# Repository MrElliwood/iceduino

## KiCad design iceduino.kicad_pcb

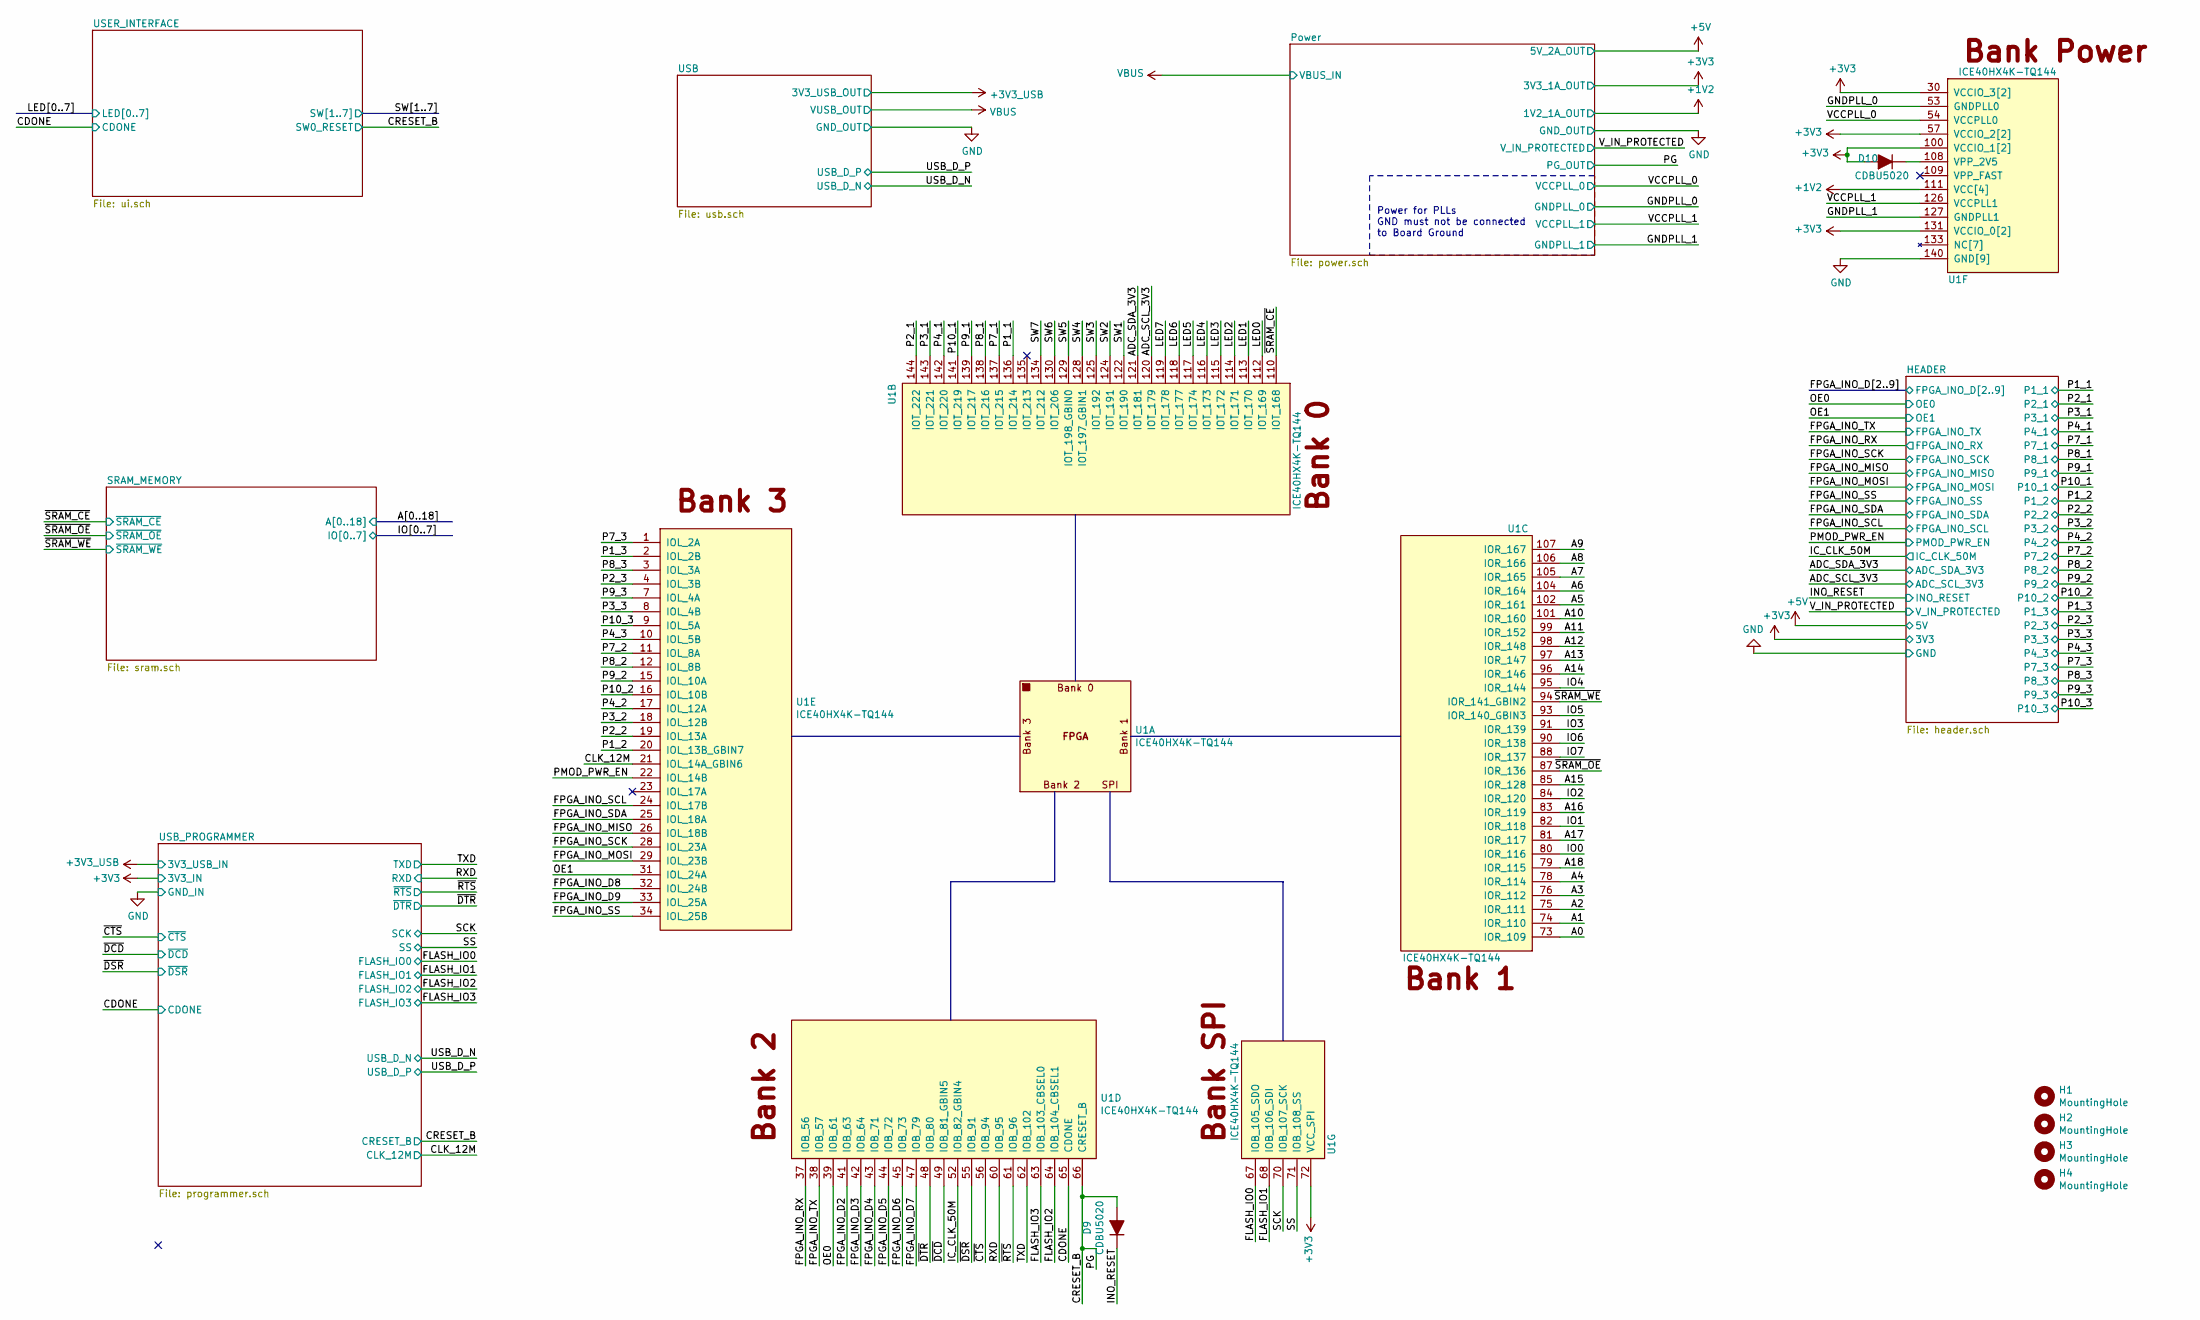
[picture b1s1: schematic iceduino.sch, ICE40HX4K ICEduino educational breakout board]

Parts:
D9, D10: CDBU5020; D_0603_1608Metric; Mfg Part Num CDBU0520; Digikey 641-1332-1-ND
H1, H2, H3, H4: MountingHole; MountingHole_3mm
U1: ICE40HX4K-TQ144; TQFP-144_20x20mm_P0.5mm; Mfg Part Num ICE40HX4K-TQ144; Digikey 220-1572-ND

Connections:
+1V2: U1.27 (VCC), U1.40 (VCC), U1.92 (VCC), U1.111 (VCC[4]); also elsewhere on the board
+3V3: D10.2 (A), U1.6 (VCCIO_3), U1.30 (VCCIO_3[2]), U1.46 (VCCIO_2), U1.57 (VCCIO_2[2]), U1.72 (VCC_SPI), U1.89 (VCCIO_1), U1.100 (VCCIO_1[2]), U1.123 (VCCIO_0), U1.131 (VCCIO_0[2]); also elsewhere on the board
/A0: U1.73 (IOR_109); also elsewhere on the board
/A1: U1.74 (IOR_110); also elsewhere on the board
/A2: U1.75 (IOR_111); also elsewhere on the board
/A3: U1.76 (IOR_112); also elsewhere on the board
/A4: U1.78 (IOR_114); also elsewhere on the board
/A5: U1.102 (IOR_161); also elsewhere on the board
/A6: U1.104 (IOR_164); also elsewhere on the board
/A7: U1.105 (IOR_165); also elsewhere on the board
/A8: U1.106 (IOR_166); also elsewhere on the board
/A9: U1.107 (IOR_167); also elsewhere on the board
/A10: U1.101 (IOR_160); also elsewhere on the board
/A11: U1.99 (IOR_152); also elsewhere on the board
/A12: U1.98 (IOR_148); also elsewhere on the board
/A13: U1.97 (IOR_147); also elsewhere on the board
/A14: U1.96 (IOR_146); also elsewhere on the board
/A15: U1.85 (IOR_128); also elsewhere on the board
/A16: U1.83 (IOR_119); also elsewhere on the board
/A17: U1.81 (IOR_117); also elsewhere on the board
/A18: U1.79 (IOR_115); also elsewhere on the board
/ADC_SCL_3V3: U1.120 (IOT_179); also elsewhere on the board
/ADC_SDA_3V3: U1.121 (IOT_181); also elsewhere on the board
/CDONE: U1.65 (CDONE); also elsewhere on the board
/CLK_12M: U1.21 (IOL_14A_GBIN6); also elsewhere on the board
/CRESET_B: D9.2 (A), U1.66 (CRESET_B); also elsewhere on the board
/FLASH_IO0: U1.67 (IOB_105_SDO); also elsewhere on the board
/FLASH_IO1: U1.68 (IOB_106_SDI); also elsewhere on the board
/FLASH_IO2: U1.64 (IOB_104_CBSEL1); also elsewhere on the board
/FLASH_IO3: U1.63 (IOB_103_CBSEL0); also elsewhere on the board
/FPGA_INO_D2: U1.41 (IOB_63); also elsewhere on the board
/FPGA_INO_D3: U1.42 (IOB_64); also elsewhere on the board
/FPGA_INO_D4: U1.43 (IOB_71); also elsewhere on the board
/FPGA_INO_D5: U1.44 (IOB_72); also elsewhere on the board
/FPGA_INO_D6: U1.45 (IOB_73); also elsewhere on the board
/FPGA_INO_D7: U1.47 (IOB_79); also elsewhere on the board
/FPGA_INO_D8: U1.32 (IOL_24B); also elsewhere on the board
/FPGA_INO_D9: U1.33 (IOL_25A); also elsewhere on the board
/FPGA_INO_MISO: U1.26 (IOL_18B); also elsewhere on the board
/FPGA_INO_MOSI: U1.29 (IOL_23B); also elsewhere on the board
/FPGA_INO_RX: U1.37 (IOB_56); also elsewhere on the board
/FPGA_INO_SCK: U1.28 (IOL_23A); also elsewhere on the board
/FPGA_INO_SCL: U1.24 (IOL_17B); also elsewhere on the board
/FPGA_INO_SDA: U1.25 (IOL_18A); also elsewhere on the board
/FPGA_INO_SS: U1.34 (IOL_25B); also elsewhere on the board
/FPGA_INO_TX: U1.38 (IOB_57); also elsewhere on the board
/GNDPLL_0: U1.53 (GNDPLL0); also elsewhere on the board
/GNDPLL_1: U1.127 (GNDPLL1); also elsewhere on the board
/IC_CLK_50M: U1.52 (IOB_82_GBIN4); also elsewhere on the board
/INO_RESET: D9.1 (K); also elsewhere on the board
/IO0: U1.80 (IOR_116); also elsewhere on the board
/IO1: U1.82 (IOR_118); also elsewhere on the board
/IO2: U1.84 (IOR_120); also elsewhere on the board
/IO3: U1.91 (IOR_139); also elsewhere on the board
/IO4: U1.95 (IOR_144); also elsewhere on the board
/IO5: U1.93 (IOR_140_GBIN3); also elsewhere on the board
/IO6: U1.90 (IOR_138); also elsewhere on the board
/IO7: U1.88 (IOR_137); also elsewhere on the board
/LED0: U1.112 (IOT_169); also elsewhere on the board
/LED1: U1.113 (IOT_170); also elsewhere on the board
/LED2: U1.114 (IOT_171); also elsewhere on the board
/LED3: U1.115 (IOT_172); also elsewhere on the board
/LED4: U1.116 (IOT_173); also elsewhere on the board
/LED5: U1.117 (IOT_174); also elsewhere on the board
/LED6: U1.118 (IOT_177); also elsewhere on the board
/LED7: U1.119 (IOT_178); also elsewhere on the board
/OE0: U1.39 (IOB_61); also elsewhere on the board
/OE1: U1.31 (IOL_24A); also elsewhere on the board
/P1_1: U1.136 (IOT_214); also elsewhere on the board
/P1_2: U1.20 (IOL_13B_GBIN7); also elsewhere on the board
/P1_3: U1.2 (IOL_2B); also elsewhere on the board
/P2_1: U1.144 (IOT_222); also elsewhere on the board
/P2_2: U1.19 (IOL_13A); also elsewhere on the board
/P2_3: U1.4 (IOL_3B); also elsewhere on the board
/P3_1: U1.143 (IOT_221); also elsewhere on the board
/P3_2: U1.18 (IOL_12B); also elsewhere on the board
/P3_3: U1.8 (IOL_4B); also elsewhere on the board
/P4_1: U1.142 (IOT_220); also elsewhere on the board
/P4_2: U1.17 (IOL_12A); also elsewhere on the board
/P4_3: U1.10 (IOL_5B); also elsewhere on the board
/P7_1: U1.137 (IOT_215); also elsewhere on the board
/P7_2: U1.11 (IOL_8A); also elsewhere on the board
/P7_3: U1.1 (IOL_2A); also elsewhere on the board
/P8_1: U1.138 (IOT_216); also elsewhere on the board
/P8_2: U1.12 (IOL_8B); also elsewhere on the board
/P8_3: U1.3 (IOL_3A); also elsewhere on the board
/P9_1: U1.139 (IOT_217); also elsewhere on the board
/P9_2: U1.15 (IOL_10A); also elsewhere on the board
/P9_3: U1.7 (IOL_4A); also elsewhere on the board
/P10_1: U1.141 (IOT_219); also elsewhere on the board
/P10_2: U1.16 (IOL_10B); also elsewhere on the board
/P10_3: U1.9 (IOL_5A); also elsewhere on the board
/PMOD_PWR_EN: U1.22 (IOL_14B); also elsewhere on the board
/RXD: U1.60 (IOB_95); also elsewhere on the board
/SCK: U1.70 (IOB_107_SCK); also elsewhere on the board
/SS: U1.71 (IOB_108_SS); also elsewhere on the board
/SW1: U1.122 (IOT_190); also elsewhere on the board
/SW2: U1.124 (IOT_191); also elsewhere on the board
/SW3: U1.125 (IOT_192); also elsewhere on the board
/SW4: U1.128 (IOT_197_GBIN1); also elsewhere on the board
/SW5: U1.129 (IOT_198_GBIN0); also elsewhere on the board
/SW6: U1.130 (IOT_206); also elsewhere on the board
/SW7: U1.134 (IOT_212); also elsewhere on the board
/TXD: U1.62 (IOB_102); also elsewhere on the board
/VCCPLL_0: U1.54 (VCCPLL0); also elsewhere on the board
/VCCPLL_1: U1.126 (VCCPLL1); also elsewhere on the board
/~CTS~: U1.56 (IOB_94); also elsewhere on the board
/~DCD~: U1.49 (IOB_81_GBIN5); also elsewhere on the board
/~DSR~: U1.55 (IOB_91); also elsewhere on the board
/~DTR~: U1.48 (IOB_80); also elsewhere on the board
/~RTS~: U1.61 (IOB_96); also elsewhere on the board
/~SRAM_CE~: U1.110 (IOT_168); also elsewhere on the board
/~SRAM_OE~: U1.87 (IOR_136); also elsewhere on the board
/~SRAM_WE~: U1.94 (IOR_141_GBIN2); also elsewhere on the board
GND: U1.5 (GND), U1.13 (GND), U1.14 (GND), U1.59 (GND), U1.69 (GND), U1.86 (GND), U1.103 (GND), U1.132 (GND), U1.140 (GND[9]); also elsewhere on the board
unnamed: D10.1 (K), U1.108 (VPP_2V5)
unnamed: U1.35 (NC), U1.36 (NC), U1.50 (NC), U1.51 (NC), U1.58 (NC), U1.77 (NC), U1.133 (NC[7])

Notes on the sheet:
Power for PLLs GND must not be connected to Board Ground

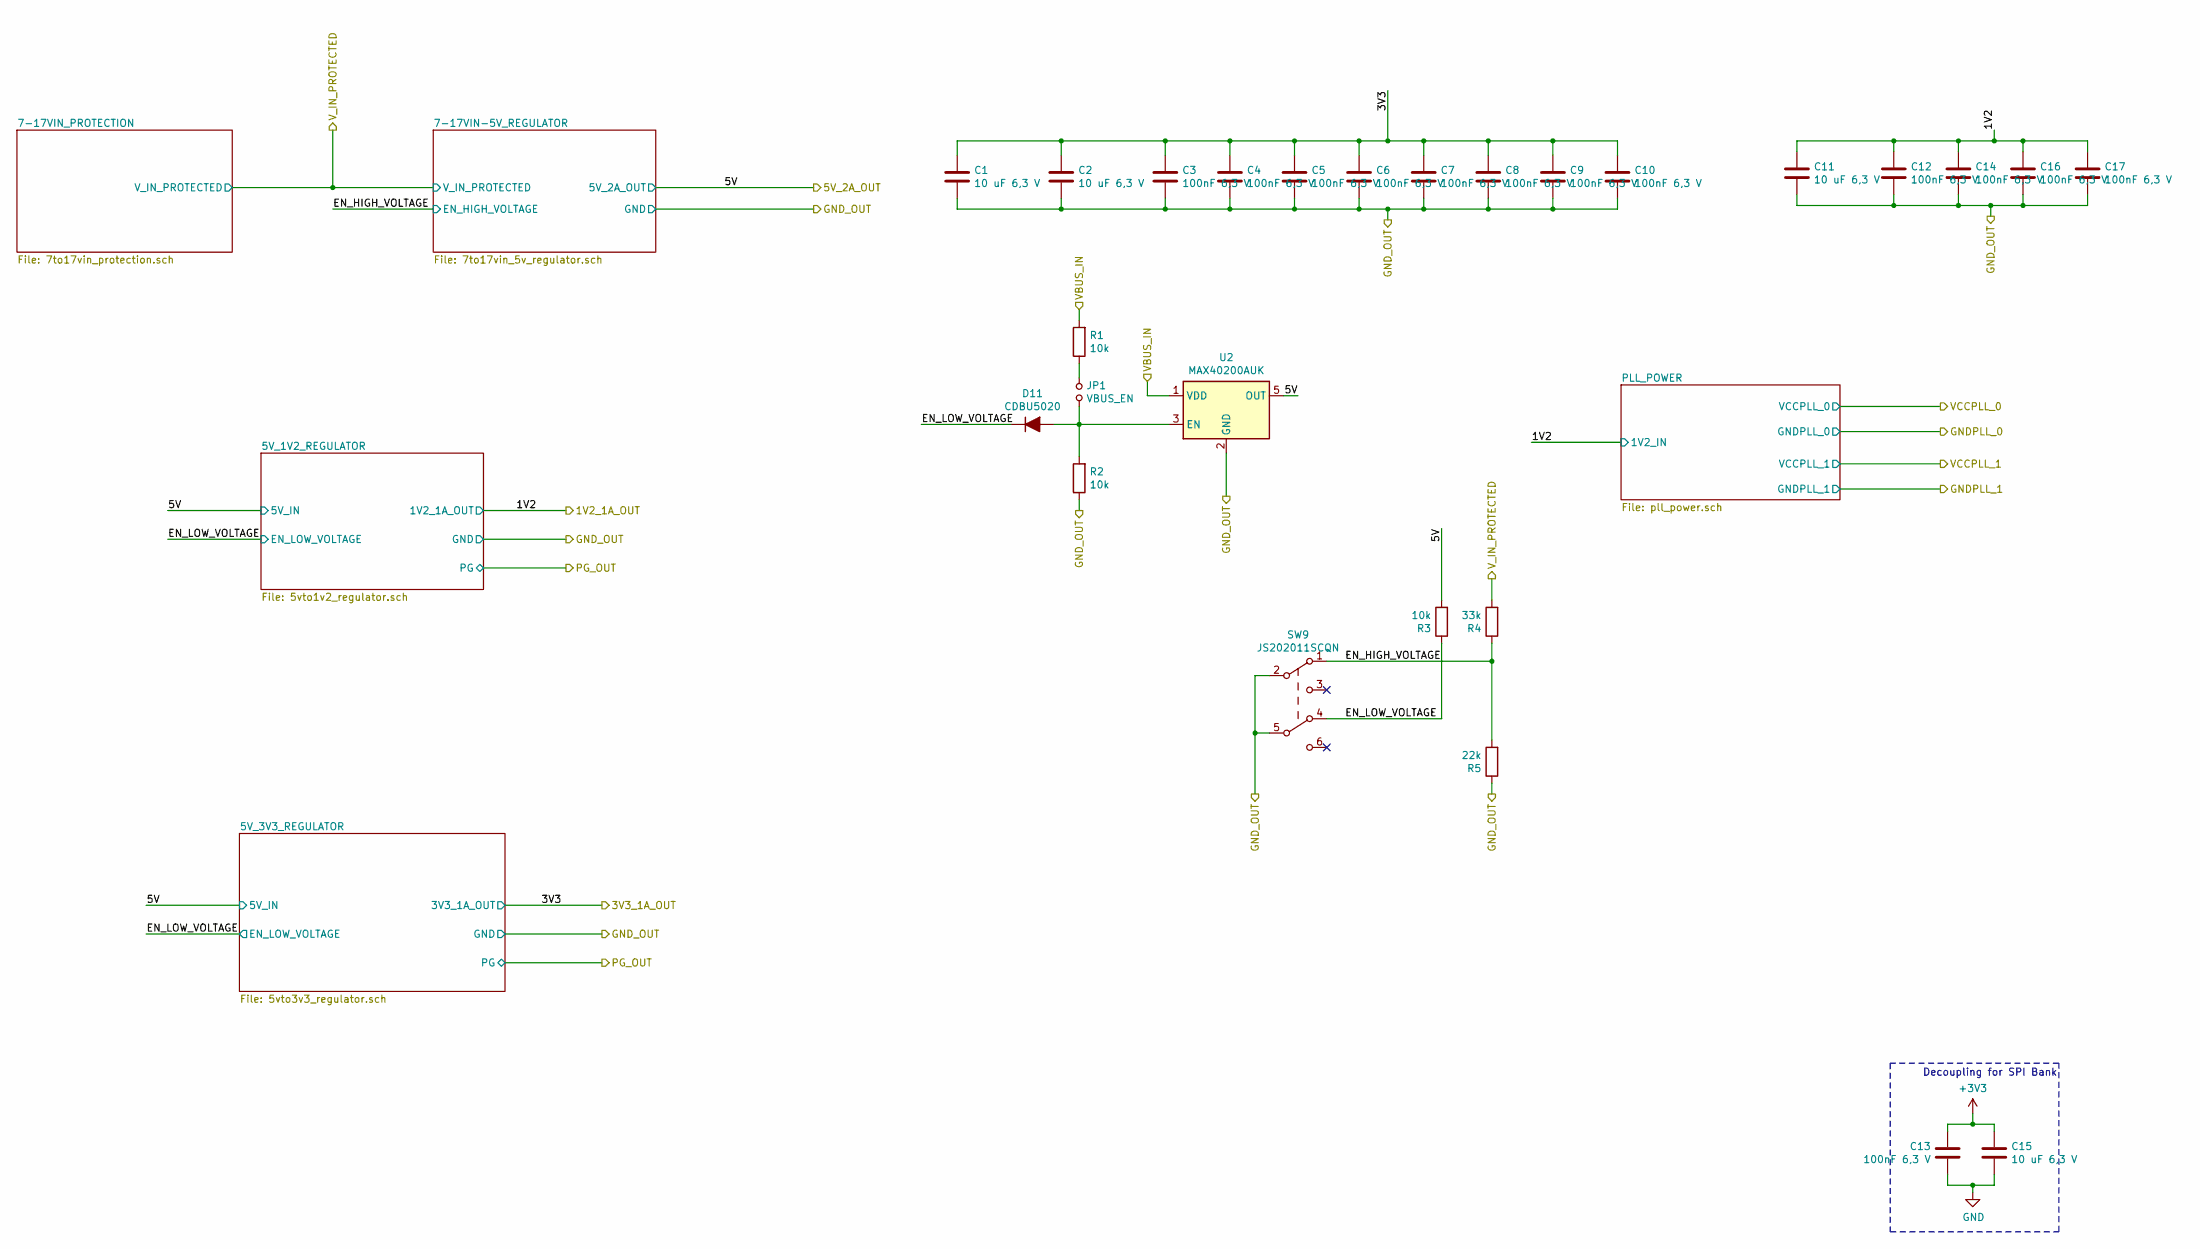
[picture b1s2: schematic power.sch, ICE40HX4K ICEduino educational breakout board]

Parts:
C1, C2, C11, C15: 10 uF 6,3 V; C_0603_1608Metric; Mfg Part Num CL10A106MQ8NNNC; Digikey 1276-1119-1-ND
C3, C4, C5, C6, C7, C8, C9, C10, C12, C13, C14, C16, C17: 100nF 6,3 V; C_0603_1608Metric; Mfg Part Num CL10B104KB8NNNC; Digikey 1276-1000-1-ND
D11: CDBU5020; D_0603_1608Metric; Mfg Part Num CDBU0520; Digikey 641-1332-1-ND
JP1: VBUS_EN; PinHeader_1x02_P2.54mm_Vertical
R1, R2, R3: 10k; R_0603_1608Metric; Mfg Part Num RMCF0603JT10K0; Digikey RMCF0603JT10K0CT-ND
R4: 33k; R_0603_1608Metric; Mfg Part Num RC0603JR-0733KL; Digikey 311-33KGRCT-ND
R5: 22k; R_0603_1608Metric; Mfg Part Num RC0603FR-0722KL; Digikey 311-22.0KHRCT-ND
SW9: JS202011SCQN; SW_SLIDE_DPDT_Slide_CK_JS202011SCQN_W3mm_P2.5mm_footprint; Mfg Part Num JS202011SCQN; Digikey 401-2002-1-ND
U2: MAX40200AUK; SOT-23-5; Mfg Part Num MAX40200AUK+T; Digikey MAX40200AUK+TCT-ND

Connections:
+1V2: C11.1, C12.1, C14.1, C16.1, C17.1; also elsewhere on the board
+3V3: C1.1, C2.1, C3.1, C4.1, C5.1, C6.1, C7.1, C8.1, C9.1, C10.1, C13.1, C15.1; also elsewhere on the board
+5V: R3.2, U2.5 (OUT); also elsewhere on the board
/Power/EN_HIGH_VOLTAGE: R4.1, R5.2, SW9.1 (A); also elsewhere on the board
/Power/EN_LOW_VOLTAGE: D11.1 (K), R3.1, SW9.4 (A); also elsewhere on the board
/V_IN_PROTECTED: R4.2; also elsewhere on the board
GND: C1.2, C2.2, C3.2, C4.2, C5.2, C6.2, C7.2, C8.2, C9.2, C10.2, C11.2, C12.2, C13.2, C14.2, C15.2, C16.2, C17.2, R2.1, R5.1, SW9.2 (B), SW9.5 (B), U2.2 (GND); also elsewhere on the board
unnamed: D11.2 (A), JP1.2, R2.2, U2.3 (EN)
unnamed: JP1.1, R1.1
VBUS: R1.2, U2.1 (VDD); also elsewhere on the board

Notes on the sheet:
Decoupling for SPI Bank

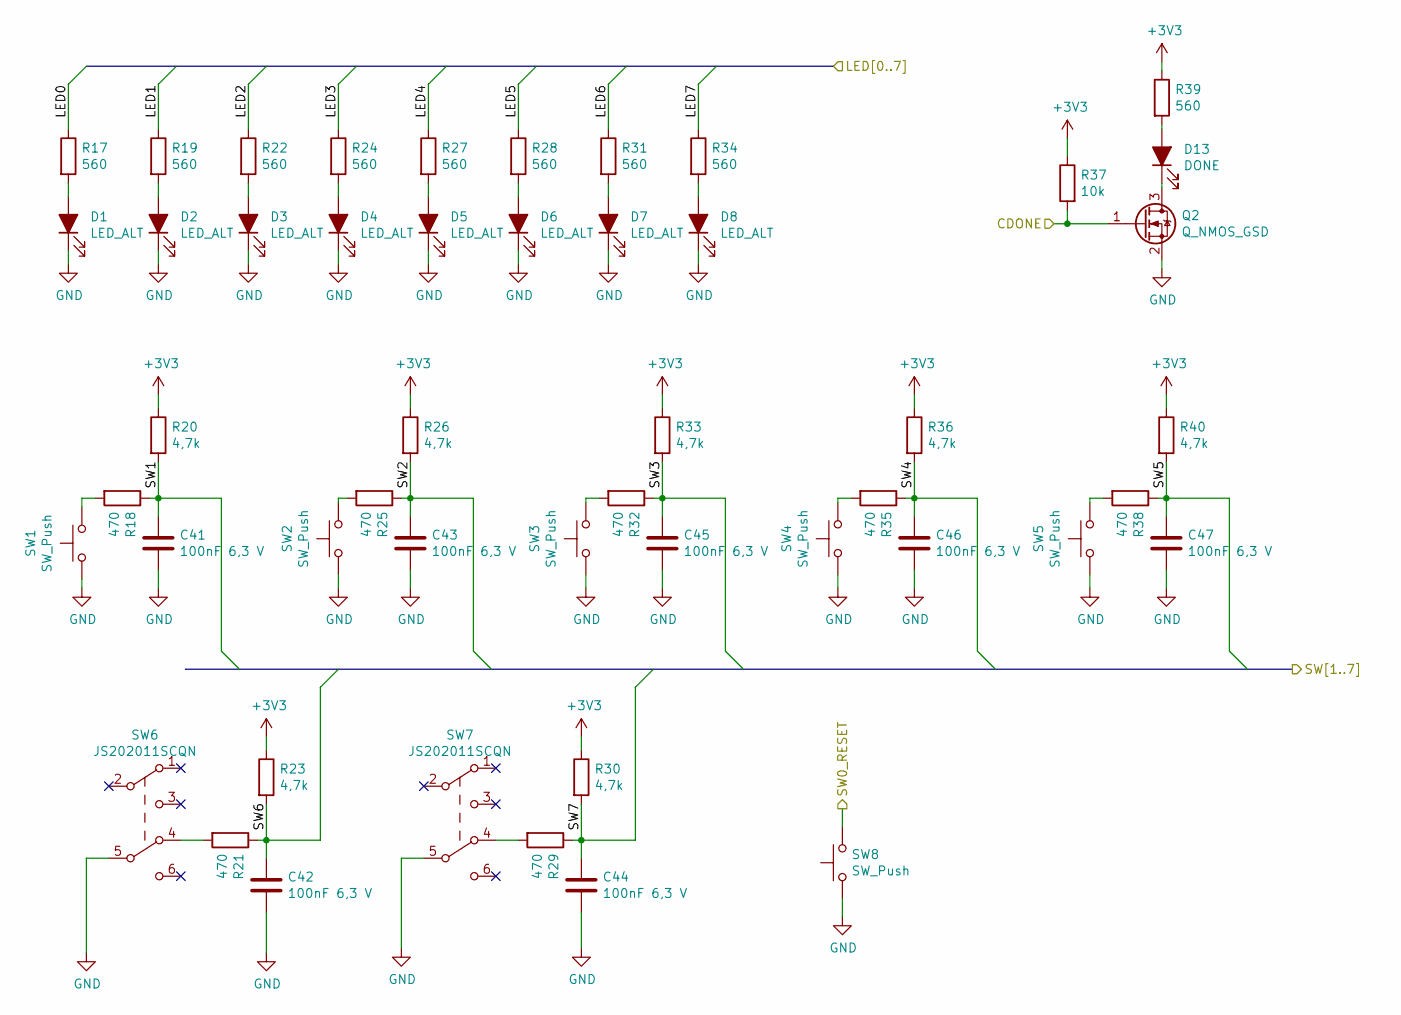
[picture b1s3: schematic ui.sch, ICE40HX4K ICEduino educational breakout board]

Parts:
C41, C42, C43, C44, C45, C46, C47: 100nF 6,3 V; C_0603_1608Metric; Mfg Part Num CL10B104KB8NNNC; Digikey 1276-1000-1-ND
D1, D2, D3, D4, D5, D6, D7, D8: LED_ALT; LED_0603_1608Metric; Mfg Part Num SML-D12U1WT86; Digikey SML-D12U1WT86CT-ND
D13: DONE; LED_0603_1608Metric; Mfg Part Num SML-D12U1WT86; Digikey SML-D12U1WT86CT-ND
Q2: Q_NMOS_GSD; SOT-23; Mfg Part Num DMN65D8L-7; Digikey DMN65D8L-7DICT-ND
R17, R19, R22, R24, R27, R28, R31, R34, R39: 560; R_0603_1608Metric; Mfg Part Num RK73B1JTTD561J; Digikey 2019-RK73B1JTTD561JCT-ND
R18, R21, R25, R29, R32, R35, R38: 470; R_0603_1608Metric; Mfg Part Num RMCF0603JT470R; Digikey RMCF0603JT470RCT-ND
R20, R23, R26, R30, R33, R36, R40: 4,7k; R_0603_1608Metric; Mfg Part Num RMCF0603JT4K70; Digikey RMCF0603JT4K70CT-ND
R37: 10k; R_0603_1608Metric; Mfg Part Num RMCF0603JT10K0; Digikey RMCF0603JT10K0CT-ND
SW1, SW2, SW3, SW4, SW5, SW8: SW_Push; SW_SPST_TL3305A; Mfg Part Num TL3305AF160QG; Digikey EG5350CT-ND
SW6, SW7: JS202011SCQN; SW_SLIDE_DPDT_Slide_CK_JS202011SCQN_W3mm_P2.5mm_footprint; Mfg Part Num JS202011SCQN; Digikey 401-2002-1-ND

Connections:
+3V3: R20.1, R23.1, R26.1, R30.1, R33.1, R36.1, R37.1, R39.1, R40.1; also elsewhere on the board
/CDONE: Q2.1 (G), R37.2; also elsewhere on the board
/CRESET_B: SW8.2; also elsewhere on the board
/LED0: R17.1; also elsewhere on the board
/LED1: R19.1; also elsewhere on the board
/LED2: R22.1; also elsewhere on the board
/LED3: R24.1; also elsewhere on the board
/LED4: R27.1; also elsewhere on the board
/LED5: R28.1; also elsewhere on the board
/LED6: R31.1; also elsewhere on the board
/LED7: R34.1; also elsewhere on the board
/SW1: C41.1, R18.1, R20.2; also elsewhere on the board
/SW2: C43.1, R25.1, R26.2; also elsewhere on the board
/SW3: C45.1, R32.1, R33.2; also elsewhere on the board
/SW4: C46.1, R35.1, R36.2; also elsewhere on the board
/SW5: C47.1, R38.1, R40.2; also elsewhere on the board
/SW6: C42.1, R21.1, R23.2; also elsewhere on the board
/SW7: C44.1, R29.1, R30.2; also elsewhere on the board
GND: C41.2, C42.2, C43.2, C44.2, C45.2, C46.2, C47.2, D1.1 (K), D2.1 (K), D3.1 (K), D4.1 (K), D5.1 (K), D6.1 (K), D7.1 (K), D8.1 (K), Q2.2 (S), SW1.1, SW2.1, SW3.1, SW4.1, SW5.1, SW6.5 (B), SW7.5 (B), SW8.1; also elsewhere on the board
unnamed: D1.2 (A), R17.2
unnamed: D2.2 (A), R19.2
unnamed: D3.2 (A), R22.2
unnamed: D4.2 (A), R24.2
unnamed: D5.2 (A), R27.2
unnamed: D6.2 (A), R28.2
unnamed: D7.2 (A), R31.2
unnamed: D8.2 (A), R34.2
unnamed: D13.1 (K), Q2.3 (D)
unnamed: D13.2 (A), R39.2
unnamed: R18.2, SW1.2
unnamed: R21.2, SW6.4 (A)
unnamed: R25.2, SW2.2
unnamed: R29.2, SW7.4 (A)
unnamed: R32.2, SW3.2
unnamed: R35.2, SW4.2
unnamed: R38.2, SW5.2

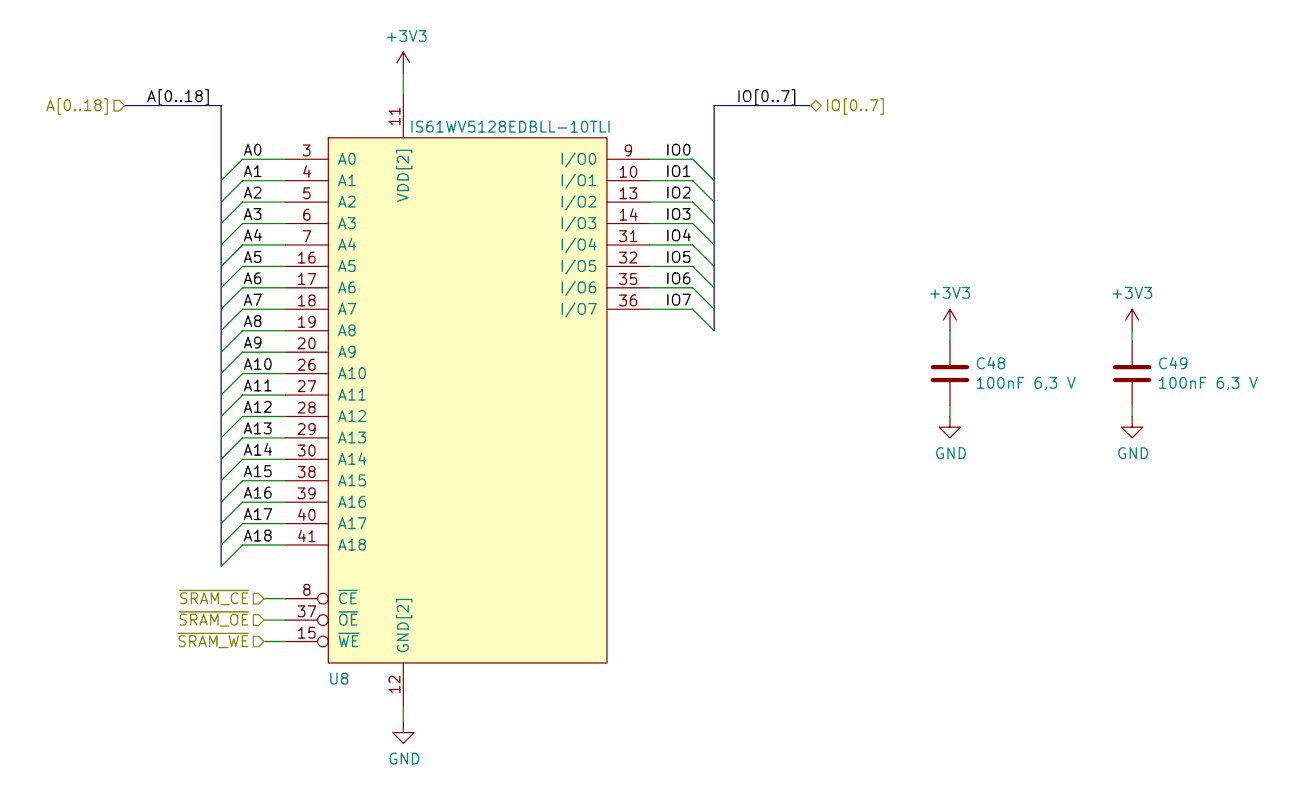
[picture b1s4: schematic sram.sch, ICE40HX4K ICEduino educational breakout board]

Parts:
C48, C49: 100nF 6,3 V; C_0603_1608Metric; Mfg Part Num CL10B104KB8NNNC; Digikey 1276-1000-1-ND
U8: IS61WV5128EDBLL-10TLI; TSOP-II-44_10.16x18.41mm_P0.8mm; Mfg Part Num IS61WV5128EDBLL-10TLI; Digikey 706-1147-ND

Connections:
+3V3: C48.1, C49.1, U8.11 (VDD[2]), U8.33 (VDD); also elsewhere on the board
/A0: U8.3 (A0); also elsewhere on the board
/A1: U8.4 (A1); also elsewhere on the board
/A2: U8.5 (A2); also elsewhere on the board
/A3: U8.6 (A3); also elsewhere on the board
/A4: U8.7 (A4); also elsewhere on the board
/A5: U8.16 (A5); also elsewhere on the board
/A6: U8.17 (A6); also elsewhere on the board
/A7: U8.18 (A7); also elsewhere on the board
/A8: U8.19 (A8); also elsewhere on the board
/A9: U8.20 (A9); also elsewhere on the board
/A10: U8.26 (A10); also elsewhere on the board
/A11: U8.27 (A11); also elsewhere on the board
/A12: U8.28 (A12); also elsewhere on the board
/A13: U8.29 (A13); also elsewhere on the board
/A14: U8.30 (A14); also elsewhere on the board
/A15: U8.38 (A15); also elsewhere on the board
/A16: U8.39 (A16); also elsewhere on the board
/A17: U8.40 (A17); also elsewhere on the board
/A18: U8.41 (A18); also elsewhere on the board
/IO0: U8.9 (I/O0); also elsewhere on the board
/IO1: U8.10 (I/O1); also elsewhere on the board
/IO2: U8.13 (I/O2); also elsewhere on the board
/IO3: U8.14 (I/O3); also elsewhere on the board
/IO4: U8.31 (I/O4); also elsewhere on the board
/IO5: U8.32 (I/O5); also elsewhere on the board
/IO6: U8.35 (I/O6); also elsewhere on the board
/IO7: U8.36 (I/O7); also elsewhere on the board
/~SRAM_CE~: U8.8 (~CE~); also elsewhere on the board
/~SRAM_OE~: U8.37 (~OE~); also elsewhere on the board
/~SRAM_WE~: U8.15 (~WE~); also elsewhere on the board
GND: C48.2, C49.2, U8.12 (GND[2]), U8.34 (GND); also elsewhere on the board

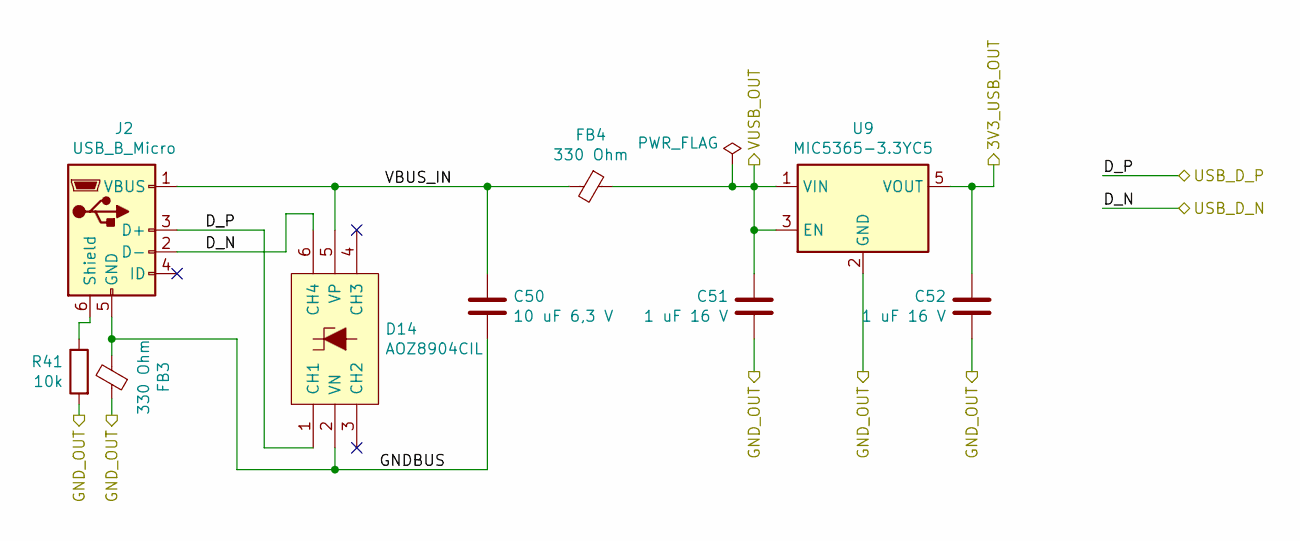
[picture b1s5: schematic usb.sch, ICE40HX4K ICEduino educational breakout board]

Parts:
C50: 10 uF 6,3 V; C_0603_1608Metric; Mfg Part Num CL10A106MQ8NNNC; Digikey 1276-1119-1-ND
C51, C52: 1 uF 16 V; C_0603_1608Metric; Mfg Part Num CL10B105MO8NNWC; Digikey 1276-6524-1-ND
D14: AOZ8904CIL; SOT-23-6; Mfg Part Num AOZ8904CIL; Digikey 785-1755-1-ND
FB3, FB4: 330 Ohm; R_0805_2012Metric; Mfg Part Num MPZ2012S331AT000; Digikey 445-1569-1-ND
J2: USB_B_Micro; Amphenol_microUSB_B_footprint; Mfg Part Num 10118194-0001LF; Digikey 609-4618-1-ND
R41: 10k; R_0603_1608Metric; Mfg Part Num RMCF0603JT10K0; Digikey RMCF0603JT10K0CT-ND
U9: MIC5365-3.3YC5; SOT-353_SC-70-5; Mfg Part Num MIC5365-3.3YC5-TR; Digikey 576-3193-1-ND

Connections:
+3V3_FTDI: C52.1, U9.5 (VOUT); also elsewhere on the board
/USB/GNDBUS: C50.2, D14.2 (VN), FB3.2, J2.5 (GND)
/USB/VBUS_IN: C50.1, D14.5 (VP), FB4.2, J2.1 (VBUS)
/USB_D_N: D14.6 (CH4), J2.2 (D-); also elsewhere on the board
/USB_D_P: D14.1 (CH1), J2.3 (D+); also elsewhere on the board
GND: C51.2, C52.2, FB3.1, R41.2, U9.2 (GND); also elsewhere on the board
unnamed: J2.6 (Shield), R41.1
VBUS: C51.1, FB4.1, U9.1 (VIN), U9.3 (EN); also elsewhere on the board

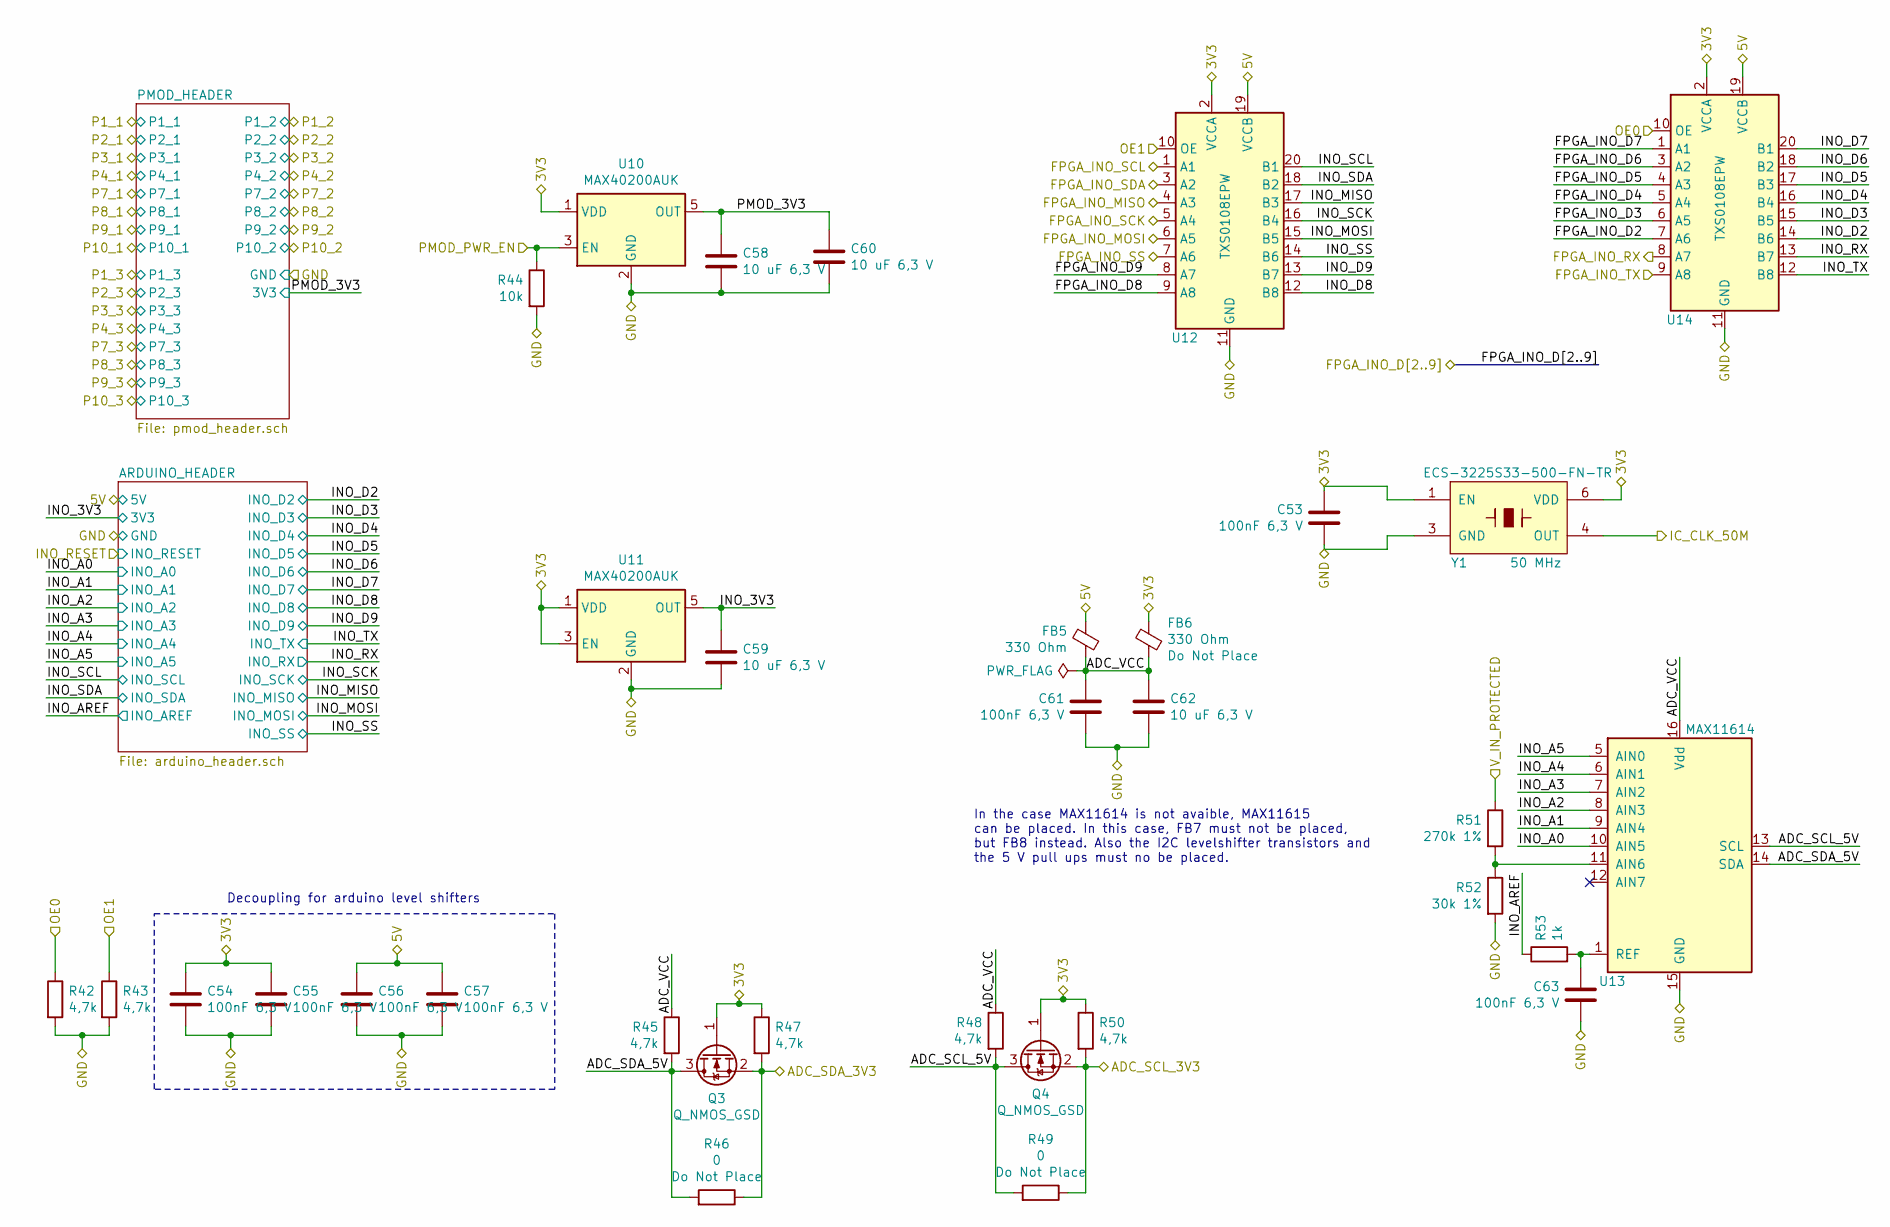
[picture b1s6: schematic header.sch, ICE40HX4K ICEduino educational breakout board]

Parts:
C53, C54, C55, C56, C57, C61, C63: 100nF 6,3 V; C_0603_1608Metric; Mfg Part Num CL10B104KB8NNNC; Digikey 1276-1000-1-ND
C58, C59, C60, C62: 10 uF 6,3 V; C_0603_1608Metric; Mfg Part Num CL10A106MQ8NNNC; Digikey 1276-1119-1-ND
FB5, FB6: 330 Ohm; R_0805_2012Metric; Mfg Part Num MPZ2012S331AT000; Digikey 445-1569-1-ND
Q3, Q4: Q_NMOS_GSD; SOT-23; Mfg Part Num DMN65D8L-7; Digikey DMN65D8L-7DICT-ND
R42, R43, R45, R47, R48, R50: 4,7k; R_0603_1608Metric; Mfg Part Num RMCF0603JT4K70; Digikey RMCF0603JT4K70CT-ND
R44: 10k; R_0603_1608Metric; Mfg Part Num RMCF0603JT10K0; Digikey RMCF0603JT10K0CT-ND
R46, R49: 0; R_0603_1608Metric
R51: 270k 1%; R_0603_1608Metric; Mfg Part Num RC0603FR-07270KL; Digikey 311-270KHRCT-ND
R52: 30k 1%; R_0603_1608Metric; Mfg Part Num RC0603FR-0730KL; Digikey 311-30.0KHRCT-ND
R53: 1k; R_0603_1608Metric; Mfg Part Num RC0603JR-071KL; Digikey 311-1.0KGRCT-ND
U10, U11: MAX40200AUK; SOT-23-5; Mfg Part Num MAX40200AUK+T; Digikey MAX40200AUK+TCT-ND
U12, U14: TXS0108EPW; TSSOP-20_4.4x6.5mm_P0.65mm; Mfg Part Num TXS0108EPWR; Digikey 296-23011-1-ND
U13: MAX11614; QSOP-16_3.9x4.9mm_P0.635mm; Mfg Part Num MAX11614EEE+; Digikey MAX11614EEE+-ND
Y1: ECS-3225S33-500-FN-TR; Y_ECS-3225S_3.2x2.5mm_footprint; Mfg Part Num ECS-3225S33-500-FN-TR; Digikey XC2226CT-ND

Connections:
+3V3: C53.1, C54.1, C55.1, FB6.2, Q3.1 (G), Q4.1 (G), R47.1, R50.1, U10.1 (VDD), U11.1 (VDD), U11.3 (EN), U12.2 (VCCA), U14.2 (VCCA), Y1.1 (EN), Y1.6 (VDD); also elsewhere on the board
+5V: C56.1, C57.1, FB5.2, U12.19 (VCCB), U14.19 (VCCB); also elsewhere on the board
/ADC_SCL_3V3: Q4.2 (S), R49.1, R50.2; also elsewhere on the board
/ADC_SDA_3V3: Q3.2 (S), R46.1, R47.2; also elsewhere on the board
/FPGA_INO_D2: U14.7 (A6); also elsewhere on the board
/FPGA_INO_D3: U14.6 (A5); also elsewhere on the board
/FPGA_INO_D4: U14.5 (A4); also elsewhere on the board
/FPGA_INO_D5: U14.4 (A3); also elsewhere on the board
/FPGA_INO_D6: U14.3 (A2); also elsewhere on the board
/FPGA_INO_D7: U14.1 (A1); also elsewhere on the board
/FPGA_INO_D8: U12.9 (A8); also elsewhere on the board
/FPGA_INO_D9: U12.8 (A7); also elsewhere on the board
/FPGA_INO_MISO: U12.4 (A3); also elsewhere on the board
/FPGA_INO_MOSI: U12.6 (A5); also elsewhere on the board
/FPGA_INO_RX: U14.8 (A7); also elsewhere on the board
/FPGA_INO_SCK: U12.5 (A4); also elsewhere on the board
/FPGA_INO_SCL: U12.1 (A1); also elsewhere on the board
/FPGA_INO_SDA: U12.3 (A2); also elsewhere on the board
/FPGA_INO_SS: U12.7 (A6); also elsewhere on the board
/FPGA_INO_TX: U14.9 (A8); also elsewhere on the board
/HEADER/ADC_SCL_5V: Q4.3 (D), R48.2, R49.2, U13.13 (SCL)
/HEADER/ADC_SDA_5V: Q3.3 (D), R45.2, R46.2, U13.14 (SDA)
/HEADER/ADC_VCC: C61.1, C62.1, FB5.1, FB6.1, R45.1, R48.1, U13.16 (Vdd)
/HEADER/INO_3V3: C59.1, U11.5 (OUT); also elsewhere on the board
/HEADER/INO_A0: U13.10 (AIN5); also elsewhere on the board
/HEADER/INO_A1: U13.9 (AIN4); also elsewhere on the board
/HEADER/INO_A2: U13.8 (AIN3); also elsewhere on the board
/HEADER/INO_A3: U13.7 (AIN2); also elsewhere on the board
/HEADER/INO_A4: U13.6 (AIN1); also elsewhere on the board
/HEADER/INO_A5: U13.5 (AIN0); also elsewhere on the board
/HEADER/INO_AREF: R53.1; also elsewhere on the board
/HEADER/INO_D2: U14.14 (B6); also elsewhere on the board
/HEADER/INO_D3: U14.15 (B5); also elsewhere on the board
/HEADER/INO_D4: U14.16 (B4); also elsewhere on the board
/HEADER/INO_D5: U14.17 (B3); also elsewhere on the board
/HEADER/INO_D6: U14.18 (B2); also elsewhere on the board
/HEADER/INO_D7: U14.20 (B1); also elsewhere on the board
/HEADER/INO_D8: U12.12 (B8); also elsewhere on the board
/HEADER/INO_D9: U12.13 (B7); also elsewhere on the board
/HEADER/INO_MISO: U12.17 (B3); also elsewhere on the board
/HEADER/INO_MOSI: U12.15 (B5); also elsewhere on the board
/HEADER/INO_RX: U14.13 (B7); also elsewhere on the board
/HEADER/INO_SCK: U12.16 (B4); also elsewhere on the board
/HEADER/INO_SCL: U12.20 (B1); also elsewhere on the board
/HEADER/INO_SDA: U12.18 (B2); also elsewhere on the board
/HEADER/INO_SS: U12.14 (B6); also elsewhere on the board
/HEADER/INO_TX: U14.12 (B8); also elsewhere on the board
/HEADER/PMOD_3V3: C58.1, C60.1, U10.5 (OUT); also elsewhere on the board
/IC_CLK_50M: Y1.4 (OUT); also elsewhere on the board
/OE0: R42.1, U14.10 (OE); also elsewhere on the board
/OE1: R43.1, U12.10 (OE); also elsewhere on the board
/PMOD_PWR_EN: R44.1, U10.3 (EN); also elsewhere on the board
/V_IN_PROTECTED: R51.1; also elsewhere on the board
GND: C53.2, C54.2, C55.2, C56.2, C57.2, C58.2, C59.2, C60.2, C61.2, C62.2, C63.2, R42.2, R43.2, R44.2, R52.2, U10.2 (GND), U11.2 (GND), U12.11 (GND), U13.15 (GND), U14.11 (GND), Y1.3 (GND); also elsewhere on the board
unnamed: C63.1, R53.2, U13.1 (REF)
unnamed: R51.2, R52.1, U13.11 (AIN6)

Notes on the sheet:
In the case MAX11614 is not avaible, MAX11615 can be placed. In this case, FB7 must not be placed, but FB8 instead. Also the I2C levelshifter transistors and the 5 V pull ups must no be placed.
Decoupling for arduino level shifters
